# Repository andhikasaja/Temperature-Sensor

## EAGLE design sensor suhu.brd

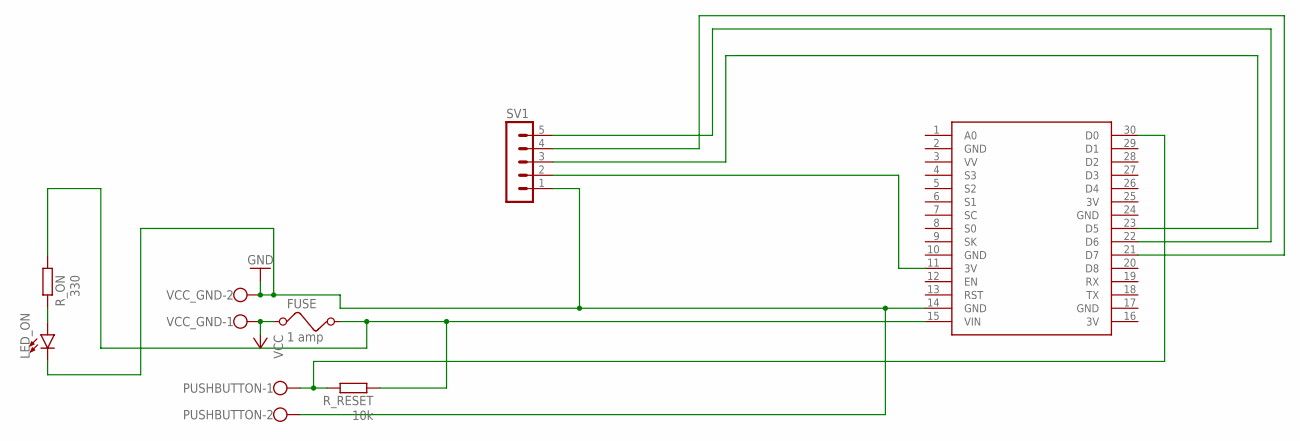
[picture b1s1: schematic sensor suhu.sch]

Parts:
FUSE: 1 amp; FUSE
LED_ON: LED5MM; LED_5MM
PUSHBUTTON: W237-102
R_ON: 330; 0207/10
R_RESET: 10k; 0207/10
SV1: MA05-1
U$1: NODEMCU
VCC_GND: W237-102

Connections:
3V: U$1.16 (3V), U$1.25 (3V)
GND: LED_ON.K (C), PUSHBUTTON.2, SV1.1, U$1.2 (GND), U$1.10 (GND), U$1.14 (GND), U$1.17 (GND), U$1.24 (GND), VCC_GND.2
unnamed: SV1.3, U$1.23 (D5)
unnamed: SV1.4, U$1.21 (D7)
unnamed: SV1.5, U$1.22 (D6)
unnamed: SV1.2, U$1.11 (3V)
unnamed: PUSHBUTTON.1, R_RESET.2, U$1.30 (D0)
unnamed: LED_ON.A, R_ON.1
VCC: FUSE.1, FUSE.2, R_ON.2, R_RESET.1, U$1.15 (VIN), VCC_GND.1

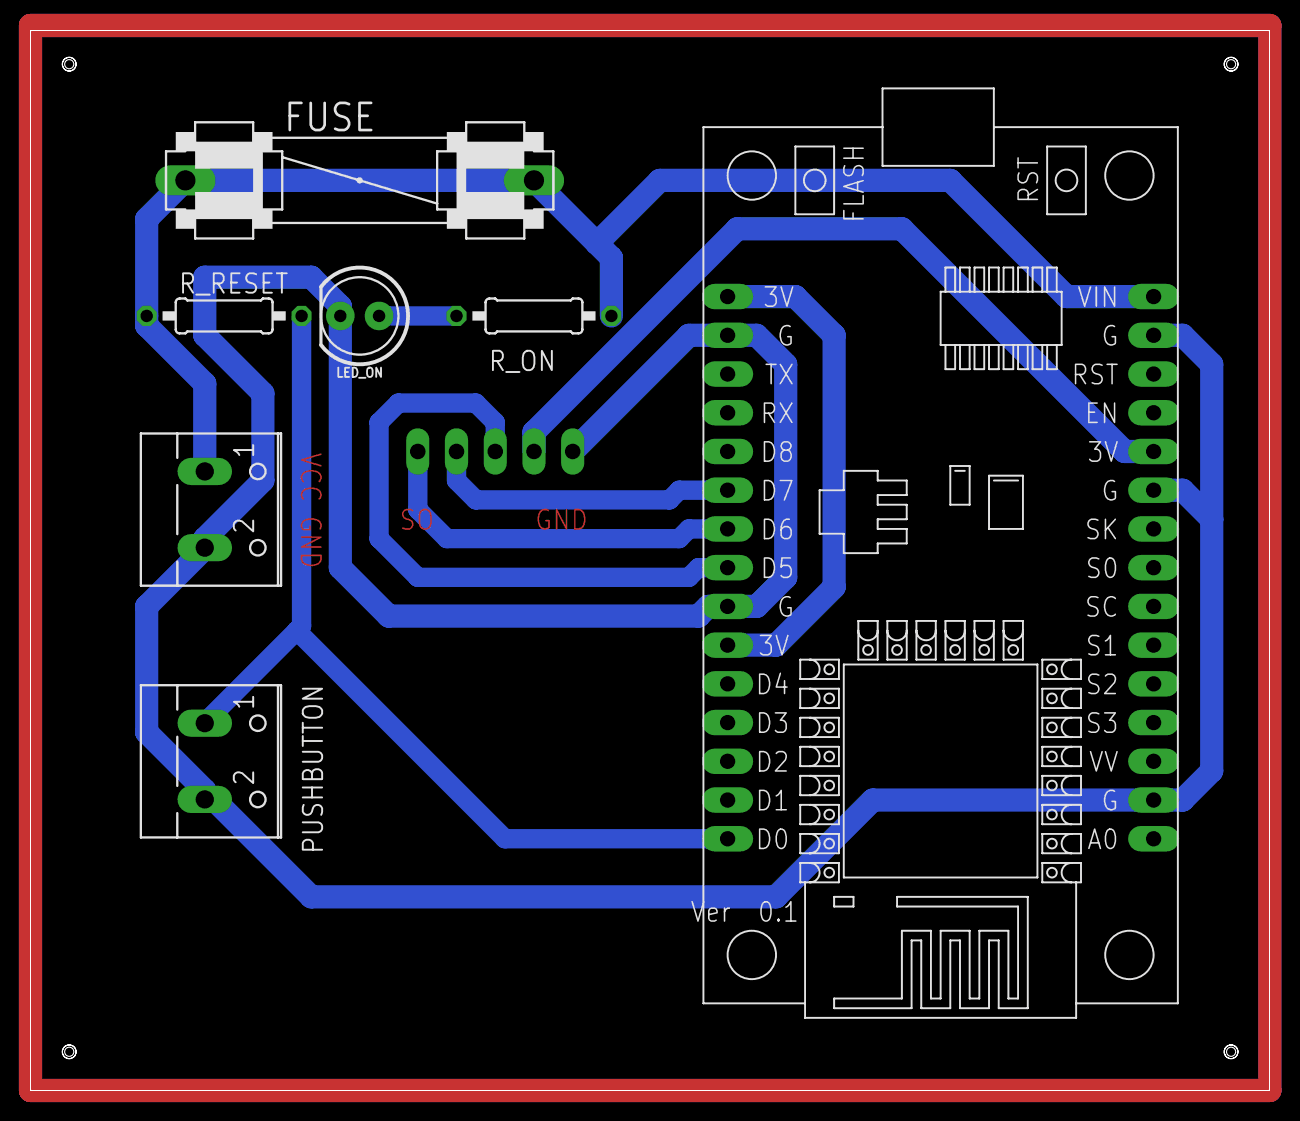
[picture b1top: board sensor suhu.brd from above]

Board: 2 copper layers, 81.3 x 69.5 mm, 8 parts (1 on the bottom side), 9 nets.

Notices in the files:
parts and their libraries:
SparkFun-LED: Licensing: Creative Commons ShareAlike 4.0 International - https://creativecommons.org/licenses/by-sa/4.0
